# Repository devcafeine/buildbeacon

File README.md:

<!-- BuildBeacon — README (English). Version 1.12 (2026-11-12) — the Hub task builds the web interface when needed. -->
# BuildBeacon

**A wall of glowing hexagonal tiles that shows the state of your GitHub Actions — and
anything else a plugin can read.**

[Version française](README.fr.md)

Each 3D-printed tile has its own LEDs. A tile follows a project: its top and bottom strips
glow with the overall state (green, red, pulsing orange while a run is in progress), and
its five dots show the last five runs. The master tile, which holds the ESP32, shows the
state of the system.

> **Status: early development.** The Hub runs from `config.json`: GitHub plugin, LED
> rendering, output to WLED, hot reload of the configuration, REST API, web interface and
> Docker image, plus a simulator and a test pattern.

## How it works

```
GitHub API ──(polling, ETag)──┐
                              ▼
              ┌──────────── Hub (Dart) ─────────────┐
              │  source plugins → state cache       │
              │        ↓                            │
              │  LED frame (20 fps)                 │──DDP/UDP──▶ ESP32 + WLED ──▶ tiles
              │  REST API · web interface           │
              └─────────────────────────────────────┘
```

- **Hardware**: WS2812B LEDs on a single data line, driven by an ESP32-C3 running
  [WLED](https://kno.wled.ge/). No custom firmware: WLED only receives the colors.
- **Hub**: a Dart program (Docker image) that reads the sources through **plugins**,
  computes the color of every LED and streams the frames to WLED over DDP.
- **Plugins**: GitHub Actions first. Anyone can add a source (another CI, a 3D printer, a
  web service…) with the plugin SDK — see [Writing a plugin](docs/writing-a-plugin.md).

## The tiles

| Tile | LEDs | Zones |
|---|---|---|
| Master (logo, holds the ESP32) | 3 | `system` |
| Project tile | 9 | `ambient`: top and bottom strips (4 LEDs) · `dots`: 5 dots (left → right) |

Tiles are chained in wiring order: the master first (LEDs 0–2), then project tile #k uses
LEDs `3 + 9·(k−1)` to `3 + 9·k − 1`. The wiring order is independent from the place on the
wall: `config.json` stores both.

Display modes: `overall` (color of the current state), `history` (last 5 runs on the dots),
`thresholds` (a measurement compared to thresholds), `gauge` (progress bar on the dots).

The 3D models (OpenSCAD) and circuit boards (KiCad) are in [`hardware/`](hardware/README.md),
under CERN-OHL-P-2.0.

## Quick start (developers)

Requirements: [mise](https://mise.jdx.dev/), which installs the right Flutter/Dart SDK.

```sh
git clone https://github.com/devcafeine/buildbeacon.git
cd buildbeacon
mise install        # Flutter 3.47.6 (Dart 3.13.5)
mise run get        # dependencies of the whole workspace
mise run check      # format, static analysis, tests
```

### Without hardware: the simulator

The simulator is a fake WLED that shows the tiles in a web page.

```sh
mise run simulator -- --open                    # terminal 1: http://localhost:8090
mise run test-pattern -- --host 127.0.0.1       # terminal 2: sends a test pattern
```

Options: `mise run simulator -- --help`. Add `--config <config.json>` to see your real
layout, `--terminal` to draw in the terminal.

### Run the Hub

```sh
mise run hub        # then open http://localhost:8080
```

`mise run hub` first builds the web interface if its code changed (a few seconds, skipped
when up to date). On its first start, the Hub creates `data/config.json` with the master
tile only. Then open
**http://localhost:8080**: the wall drawn at its real place, with the live
colors. Select a tile to choose the source and the display mode of each zone; add a tile
with a **+**, move it by dragging it, set the chain order, WLED, the brightness and the
colors. Your changes are previewed on the wall and checked by the Hub as you type; nothing
reaches the LEDs before you **save**. Language: English or French (menu, or `?lang=fr`).

#### 3D printing

The **3D printing** tab turns your wall into the parts to print with the parametric model
of [`hardware/cad`](hardware/README.md) (OpenSCAD):

- **the parts**: a shell per tile with its name (the master tile with the logo), the back
  plate of the master tile (it holds the ESP32), one back plate for the project tiles to
  print as many times as there are tiles (they are all the same), and the "dog bones" that
  join the back plates, one per side shared by two tiles;
- **Download** gives a parameter sets file named after the model
  (`buildbeacon_tile_vX.Y.json`): put it next to the `.scad` file, open the model in OpenSCAD, pick a part in the
  Customizer list, render (**F6**) and export to STL;
- or render every part at once: the tab gives the commands to run in `hardware/cad`
  (`openscad -p … -P mise-tile -o mise-tile.stl …`), with a copy button.

Style, font and mounting stay the settings of the model; the engraved name is the name of
the tile. Before the dog bones, print `part = link_test` once to adjust their fit.

To start from an example instead: [`config.example.json`](config.example.json) follows
three public projects — BuildBeacon itself (master tile), WLED and mise — and needs no
token. Copy it before starting the Hub: `mkdir -p data && cp config.example.json
data/config.json`.

**Without tiles**, the simulator plays the part of WLED in a web page: in the interface,
**Settings** tab, set the WLED address to `127.0.0.1` and save, then in another terminal:

```sh
mise run simulator -- --open --config "$PWD/data/config.json"
```

The simulator follows `data/config.json`: tiles added, moved or renamed in the interface
show up at their place, without a reload. The Hub reloads `data/config.json` as soon as it is saved, from the
interface or by hand, and refuses an invalid version (the previous one is kept).

The Hub also serves its REST API on http://localhost:8080/api (`--port` to change it):

```sh
curl http://localhost:8080/api/state        # what the tiles show, as JSON
curl -X POST http://localhost:8080/api/tiles/wled/identify \
     -H 'Content-Type: application/json' -d '{}'   # make a tile blink
```

See [REST API](docs/api.md): routes, live events, security (`BB_API_TOKEN`).

Without a token, GitHub allows 60 requests per hour: the example polls every 180 s for
its 3 sources, and the Hub tells you if your configuration needs more. With a token
(`cp .env.example .env`, then fill `BB_GITHUB_TOKEN`), you can go down to 30 s and follow
private repositories.

### With the tiles

1. Flash [WLED](https://install.wled.me/) on the ESP32-C3, then in its web interface:
   - *LED Preferences*: data GPIO 4, type WS281x, color order GRB, length = 3 + 9 × number
     of project tiles, maximum current of your power supply;
   - *WiFi Setup*: your network, mDNS name `buildbeacon` (→ `buildbeacon.local`);
   - *Sync Interfaces*: "Receive UDP realtime" enabled (default).
2. Check the wiring and find the chain order:
   `mise run test-pattern -- --host buildbeacon.local` (or the IP of WLED).
3. Run `mise run hub` and describe your tiles in the web interface: their place on the wall
   (drag them) and the wiring order (**Chain** tab; *identify* makes a tile blink). The
   Hub checks WLED (LED count) and sets its brightness.

## Where can the Hub run?

The Hub is a small native program: very little CPU, about 50 MB of RAM. It must be on the
same network as WLED (UDP 4048, HTTP 80) and reach the Internet for the sources.

| Hardware | Supported | Notes |
|---|---|---|
| Mini PC, server or NAS, Linux x86-64 | yes | recommended: always on, [with Docker](#install-with-docker-linux) |
| Raspberry Pi 3, 4, 5, Zero 2 W with a 64-bit OS (arm64) | yes | a good choice without a server; Docker too |
| Raspberry Pi 2 or 3 with a 32-bit OS (ARMv7) | yes | published Docker image |
| macOS, Windows, Linux desktop | yes | to develop or try it out |
| Raspberry Pi 1, Zero, Zero W (ARMv6) | no | Dart does not support ARMv6 |
| ESP32 and other microcontrollers | no | the ESP32 runs WLED and only receives the colors |

Tested so far: macOS (Apple Silicon), Linux x86-64 (CI) and the Docker image (x86-64 in
the CI, arm64 with OrbStack; arm64 and ARMv7 images built and published by the CI). The other platforms
are supported by Dart but not tested yet: reports are welcome.

## Install with Docker (Linux)

The recommended setup: an always-on Linux machine on the same network as WLED — mini PC,
server, Raspberry Pi 4 or 5 with a 64-bit OS.

The image is published on GitHub for x86-64, arm64 and ARMv7
([`ghcr.io/devcafeine/buildbeacon-hub`](https://github.com/devcafeine/buildbeacon/pkgs/container/buildbeacon-hub)):
two files are enough, no need to clone the repository.

```sh
mkdir buildbeacon && cd buildbeacon
curl -fsSLO https://raw.githubusercontent.com/devcafeine/buildbeacon/main/docker-compose.yml
curl -fsSL -o .env https://raw.githubusercontent.com/devcafeine/buildbeacon/main/.env.example
# optional, in .env: BB_GITHUB_TOKEN, BB_LANG=fr, BB_PORT…
docker compose pull && docker compose up -d
```

Then open **http://<address of the machine>:8080**. On its first start, the Hub creates
its configuration with the master tile only, in the `buildbeacon-data` volume: everything
else is set up in the web interface.

- **Network**: the container uses the network of the machine (`network_mode: host`), so
  the LED frames reach WLED over UDP and `buildbeacon.local` is found by mDNS, as outside
  Docker. The interface listens on port 8080; set `BB_PORT` in `.env` to change it.
- **Update**: `docker compose pull && docker compose up -d`. **Logs**:
  `docker compose logs -f`.
- **Versions**: `latest` follows the main branch; each version also has its own tag
  (`ghcr.io/devcafeine/buildbeacon-hub:0.2.0`): put it in `docker-compose.yml` instead of
  `latest` to stay on a version, or to go back to one.
- **The image** (about 40 MB) holds the compiled Hub and its interface only, and runs as
  an unprivileged user. Secrets stay in `.env`, outside the image and the volume.
- **Build it from the sources** instead: `git clone` the repository, then
  `docker compose up -d --build` in it. It takes a few minutes the first time (it downloads
  Flutter to build the interface) and about 2 GB of RAM, on a Linux x86-64 or arm64
  machine.
- **On macOS or Windows**, Docker runs in a virtual machine: set the IP address of WLED, as
  mDNS does not reach the local network from there. To try BuildBeacon on these systems,
  `mise run hub` is simpler.

## Configuration

`config.json` (edited from the web interface, by hand or through the
[REST API](docs/api.md)):

```json
{
  "version": 1,
  "wled": { "host": "buildbeacon.local", "brightness": 128 },
  "poll_seconds": 30,
  "tiles": [
    { "id": "master", "label": "BuildBeacon", "kind": "master", "chain_index": 0,
      "pos": { "q": 0, "r": 1 }, "zones": { "system": null } },
    { "id": "app", "label": "App", "kind": "project", "chain_index": 1,
      "pos": { "q": 0, "r": 0 },
      "zones": {
        "ambient": { "source": { "type": "github", "repo": "owner/app", "workflow": "ci.yml" },
                     "mode": "overall" },
        "dots":    { "source": { "type": "github", "repo": "owner/app", "workflow": "ci.yml" },
                     "mode": "history" } } }
  ]
}
```

Secrets never go into `config.json`: the GitHub token (fine-grained, read-only, *Actions:
read* and *Metadata: read*) is given through the `BB_GITHUB_TOKEN` environment variable —
see [`.env.example`](.env.example). The REST API never returns a secret.

## Languages

The interfaces are available in English and French (`BB_LANG=en` or `BB_LANG=fr` for the
command-line tools; for the web pages, the browser language or the language menu). Plugins
bring their own translations.

## Repository

```
hub/                 Dart workspace
  sdk/               plugin SDK (the only dependency of a plugin)
  core/              model, LED rendering, plugin registry
  plugins/github/    GitHub Actions plugin
  server/            the Hub (bin/hub.dart), REST API, DDP output, simulator, test pattern
  ui/                web interface (Flutter Web), served by the Hub
  Dockerfile         Docker image of the Hub and its interface
  tool/              new_plugin.dart (mise run new-plugin <name>)
docs/                guides, REST API
hardware/            3D models (cad/), circuit boards (pcb/), build guide
config.example.json example configuration (public repositories)
docker-compose.yml  the Hub in Docker (docker compose up -d --build)
```

## Contributing

Bug reports, ideas, plugins and translations are welcome: see
[CONTRIBUTING.md](CONTRIBUTING.md) and [Writing a plugin](docs/writing-a-plugin.md).

## License

Software: [MIT](LICENSE). Hardware (3D models, boards, in `hardware/`):
[CERN-OHL-P-2.0](hardware/LICENSE). The web interface embeds the Roboto font
([Apache License 2.0](hub/ui/assets/fonts/Roboto_LICENSE.txt)).

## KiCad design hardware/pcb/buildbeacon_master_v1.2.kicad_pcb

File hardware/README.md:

<!-- BuildBeacon — hardware (English). Version 1.9 (2026-11-13) — model v1.7 -->
# BuildBeacon — hardware

[Version française](README.fr.md)

Everything you need to build the tiles: parametric 3D models (OpenSCAD) and circuit boards
(KiCad), licensed under [CERN-OHL-P-2.0](LICENSE).

> **Status:** the 3D models are printed and tested. The **v1.2** boards are ordered and
> **not yet validated** on a real tile: wait for feedback from the first build before ordering
> many, or build without boards (see [Building without boards](#building-without-boards)).

## Contents

```
hardware/
  cad/buildbeacon_tile_v1.7.scad      tiles, back plates, stand, Skådis clips… (OpenSCAD)
  pcb/buildbeacon_tuile_v1.2.kicad_pcb    project tile board (9 LEDs)
  pcb/buildbeacon_master_v1.2.kicad_pcb   master tile board (ESP32-C3 + 3 LEDs)
  pcb/gen_buildbeacon_pcb_v1.2.py     Python script that generates both boards
  images/                             KiCad 3D renders of the boards
  LICENSE                             CERN-OHL-P-2.0
```

File names and on-board labels are in French: *tuile* = tile, *ALIM* = power input,
*cavaliers* = solder jumpers, *1 goutte d'étain par bloc* = one solder blob per block.

## Overview

- Each hexagonal tile (80 mm across flats) holds a round board carrying short pieces of
  **WS2812B LED strip** (5 V, 100 LEDs/m, 10 mm wide).
- All LEDs form **a single data chain**, driven by an **ESP32-C3 SuperMini** running
  [WLED](https://kno.wled.ge/), housed in the **master** tile.
- Each board has **6 JST PH 3-pin connectors**, one per side of the hexagon (5 on the
  master: the 6th side is taken by USB). Neighbouring tiles are linked with short JST cables.
  The input and output sides are **selected with solder jumpers**, so tiles can be arranged
  in any shape.
- Same pinout on every connector: **1 = +5 V, 2 = data, 3 = GND**. Cables are "same
  direction" (pin 1 to pin 1).

| Tile | LEDs | Position in the chain |
|---|---|---|
| Master | 3 | LEDs 0 to 2 |
| Project tile no. k | 9: 2 at the top, 5 dots in the middle, 2 at the bottom | LEDs `3 + 9·(k−1)` to `3 + 9·k − 1` |

Inside a project tile, data enters the top strip (left → right), goes through the 5 dots
(right → left), then the bottom strip (left → right). The Hub knows this order.

## Circuit boards

| | Front | Back |
|---|---|---|
| **Project tile** |  |  |
| **Master** |  |  |

2-layer, 1.6 mm boards. Front: LED strips, resistors, capacitor, ESP32 (master). Back: JST
connectors and solder jumpers. Copper pours: +5 V on the front, GND on the back.

### Ordering the boards

1. Open the `.kicad_pcb` file in **KiCad 8 or 9** and save it once (KiCad reports an old
   file format: this is expected, the file is generated by a script).
2. **Press B** to fill the copper zones. *Skip this and the +5 V and GND pours will not be
   manufactured.*
3. Run the **DRC**: 0 errors expected.
4. Export Gerbers and drill files, then order: 2 layers, 1.6 mm, HASL, any colour. The
   boards are designed for hand soldering; no factory assembly is needed.

### Bill of materials

**Project tile** (per tile)

| Ref | Part | Notes |
|---|---|---|
| — | Board `buildbeacon_tuile_v1.2` | |
| RB1, RB2, RB3 | WS2812B strip, 5 V, 100 LEDs/m, 10 mm: pieces of 2, 5 and 2 LEDs | follow the "DIN >>>" arrows |
| R1 | 330 Ω resistor, ¼ W, through-hole | 220 to 470 Ω is fine |
| R2 | 10 kΩ resistor, ¼ W, through-hole | 10 to 100 kΩ is fine; prevents flicker when the input floats |
| C1 | 10 µF 16 V electrolytic capacitor, 5 mm pitch | laid flat, **+ on the square pad** |
| J1 to J6 | JST PH S3B-PH-SM4-TB (SMD, horizontal, 2 mm pitch) | only on the sides you use (at least 1 in, 1 out) |
| — | 2 solder blobs | 1 in the IN block, 1 in the OUT block |

**Master tile**

| Ref | Part | Notes |
|---|---|---|
| — | Board `buildbeacon_master_v1.2` | |
| U1 | ESP32-C3 SuperMini + pin headers | USB towards the edge marked "USB" |
| RB1 | WS2812B strip: piece of 3 LEDs | |
| D1 | 1N4148 (or 1N4001 to 1N4007) | **band towards the square pad**, see below |
| R1 | 330 Ω resistor | between GPIO 4 and the strip |
| C1 | 10 µF 16 V electrolytic | **+ on the square pad** |
| J1 to J4, J6 | JST PH S3B-PH-SM4-TB | used sides only |
| J7 | 5 V input "ALIM" (2 wires or a 5.08 mm terminal block) | optional, see [Power](#power) |
| — | 1 solder blob | OUT block |

**Common**: JST PH 3-pin double-ended "same direction" cables, M2.5 × 4 × 3.5 brass inserts
+ M2.5 × 6 screws to hold the board, M3 × 5 × 4 inserts + M3 screws (or 6 × 3 mm magnets) to
close the tile.

### Shopping list

For a setup of **1 master + N project tiles** (example: N = 4).

| Item | Quantity | Example N = 4 |
|---|---|---|
| Board `buildbeacon_master_v1.2` | 1 | 1 |
| Board `buildbeacon_tuile_v1.2` | N | 4 |
| ESP32-C3 SuperMini (with pin headers) | 1 | 1 |
| WS2812B strip, 5 V, 100 LEDs/m, 10 mm | 3 + 9 × N LEDs (1 m = 100 LEDs, up to 10 tiles) | 39 LEDs → 1 m |
| 330 Ω ¼ W resistor | N + 1 | 5 |
| 10 kΩ ¼ W resistor | N | 4 |
| 10 µF 16 V electrolytic capacitor, 5 mm pitch | N + 1 | 5 |
| 1N4148 diode (or 1N4001 to 1N4007) | 1 | 1 |
| JST PH S3B-PH-SM4-TB connector | at least 2 × N (2 per project tile, 1 on the master and on the last tile); up to 6 × N + 5 to allow any layout | 8 to 29 |
| JST PH 3-pin double-ended "same direction" cable | N (one per link between two tiles) | 4 |
| M2.5 × 4 × 3.5 brass insert + M2.5 × 6 screw (board mounting) | 4 × (N + 1) | 20 + 20 |
| Tile closing: 6 × 3 mm magnets **or** M3 × 5 × 4 inserts + M3 screws | 6 × (N + 1) magnets **or** 3 × (N + 1) inserts and screws | 30 magnets or 15 + 15 |
| USB-C cable | 1 | 1 |
| 5 V power supply (optional, on J7 "ALIM") | at least 0.6 A × N (see [Power](#power)) | 5 V 3 A |
| 2-pin 5.08 mm terminal block (optional, J7) | 1 | 1 |
| White or "natural" PLA or PETG filament | shells, back plates, links, stand or clips | |

Board makers often ship a minimum of 5 boards per design.
For [building without boards](#building-without-boards), you only need the ESP32, the
strip, one 330 Ω resistor, the tile closing parts and the power supply, plus 22 to 28 AWG
silicone wire (3 wires per link).

### Tools

- 3D printer.
- Fine-tip soldering iron (the JST connectors are SMD), solder, flux.
- Desoldering braid (to move a jumper blob).
- Scissors or a cutter to cut the LED strip on its cut marks.
- Side cutters, tweezers; a multimeter is recommended (check there is no short between +5 V
  and GND before powering up for the first time).
- A computer to install WLED on the ESP32 (see [Configuring WLED](#configuring-wled)).

### Why D1 on the master?

The ESP32 sends 3.3 V data, while LEDs powered at 5 V expect at least about 3.5 V: at high
brightness the first LED misreads the signal and the chain flickers. D1 drops the supply of
the 3 master LEDs by about 0.7 V (≈ 4.4 V): they then read the 3.3 V signal reliably and pass
it on at 5 V to the following tiles.

### Solder jumpers: choosing input and output

On the back, the jumpers are grouped in blocks of 6 rows numbered **1 to 6**, like the sides
(each side's number is printed next to its connector).

- **Project tile**: **IN** block = side where data comes in; **OUT** block = side towards the
  next tile. **One solder blob per block**, bridging the two pads of the chosen row.
  Example: data arrives on side 4 and leaves on side 1 → blob on row 4 of IN and row 1 of OUT.
- **Master**: a single **OUT** block (sides 1, 2, 3, 4 and 6).
- The last tile of the chain needs no blob in its OUT block.
- To change it: remove the blob with desoldering braid.

### Power

- **Small setup** (master + 2 or 3 tiles, limited brightness): the ESP32's USB-C is enough.
- **More tiles**: external 5 V supply on the master's **J7 "ALIM"** (square = +5 V,
  round = GND). +5 V and GND run through every JST connector.
- **Never connect USB and the external supply at the same time.** Unplug the external supply
  before flashing the ESP32.
- Budget up to 60 mA per LED at full white (≈ 0.55 A per project tile). Set WLED's current
  limiter to your supply's rating (850 to 1,500 mA on USB).
- Recommended brightness: start at 128 (50 %).

### Regenerating the boards

The boards are produced by `gen_buildbeacon_pcb_v1.2.py` (Python 3, no dependencies):

```sh
cd hardware/pcb
python3 gen_buildbeacon_pcb_v1.2.py          # project tile
python3 gen_buildbeacon_pcb_v1.2.py --logo   # master
```

Any board change bumps the script's `VERSION` variable (and so the file names and the text
printed on the back of the board).

## 3D models

A single parametric file: [`cad/buildbeacon_tile_v1.7.scad`](cad/buildbeacon_tile_v1.7.scad),
to open in [OpenSCAD](https://openscad.org/) (2021 or later). Set the parameters in the
**Customizer**, pick the part with `part`, render (**F6**) and export to STL.

**From the web interface of the Hub**: the **3D printing** tab lists the parts of your wall
(a shell per tile with its name, the back plates, the dog bones) and downloads
`buildbeacon_tile_v1.7.json`, one parameter set per part. Put it next to the `.scad` file:
the Customizer offers the sets in its list, ready to render; the tab also gives the
commands that render every part at once (`openscad -p … -P <set> -o <set>.stl`).

### Parts (`part`)

| `part` | Part |
|---|---|
| `tile` | tile shell (face with the text) |
| `back` | back plate (holds the LEDs or the board) |
| `both` | both, for preview |
| `links` / `link_test` | "dog bones" joining the back plates / 4 test bones for fit |
| `magnet_test` | pieces of two neighbouring tiles to try the tile-to-tile magnets |
| `stand` | desk stand (tiles in a row) |
| `skadis_clips` | clips for an IKEA Skådis pegboard |
| `cable_clips`, `plugs` | cable clips, notch plugs |
| `letters`, `base`, `led_bridge`, `knockout_test` | options (see the comments in the file) |

### Main settings

- **Text**: `label` (project name), `label2`, `font`, `text_size`. Master tile:
  `master = true` and `master_logo = true` (logo instead of a name).
- **Style**: `glow` (one colour, thinned text shines brighter), `swap` (filament change:
  black face, white letters), `dark_face`, `stencil`.
- **With the boards**: `led_mount = "pcb"`, `pcb_fix = "insert"` (M2.5 × 4 × 3.5 inserts,
  hole `pcb_insert_d = 3.2`).
- **Closing the tile**: `screw_type = "magnet"` (6 × 3 mm magnets) or `"insert"` (M3 × 5 × 4
  inserts, hole `insert_d = 3.6`).
- **Joining the plates**: `link_fit` sets how tight the dog bones are; print
  `part = "link_test"` first to find the right value.
- **Tile-to-tile magnets** (being tested, off by default): `link_magnets = true` puts one
  6 × 3 mm magnet per side in a boss of the back plate, behind a 0.6 mm skin of the shell
  (`link_mag_skin`): tiles snap together and come off one by one, nothing shows outside.
  Print `part = "magnet_test"` first: it checks the fit and the hold (instructions in the
  comments of the file).

### Printing

- White or "natural" PLA or PETG for the shell (light shines through the face).
- Shell: **face down on the bed**, no supports. Back plate: ribs up. Stand and clips: flat.
- Brass inserts go in with a soldering iron (≈ 220 °C for PLA).

## Building without boards

With `led_mount = "strip"`, the strip pieces are glued straight onto the back plate between
rails and wired together (3 silicone wires, 22 to 28 AWG). Same chain order, same LEDs, no
boards to order. Add a 330 Ω resistor between the ESP32's GPIO 4 and the first LED.

## Configuring WLED

See the [main README](../README.md#with-the-tiles): GPIO 4, WS281x, GRB order,
length = 3 + 9 × number of project tiles, current limiter set.

## License

Hardware (this folder): [CERN-OHL-P-2.0](LICENSE). Software: [MIT](../LICENSE).

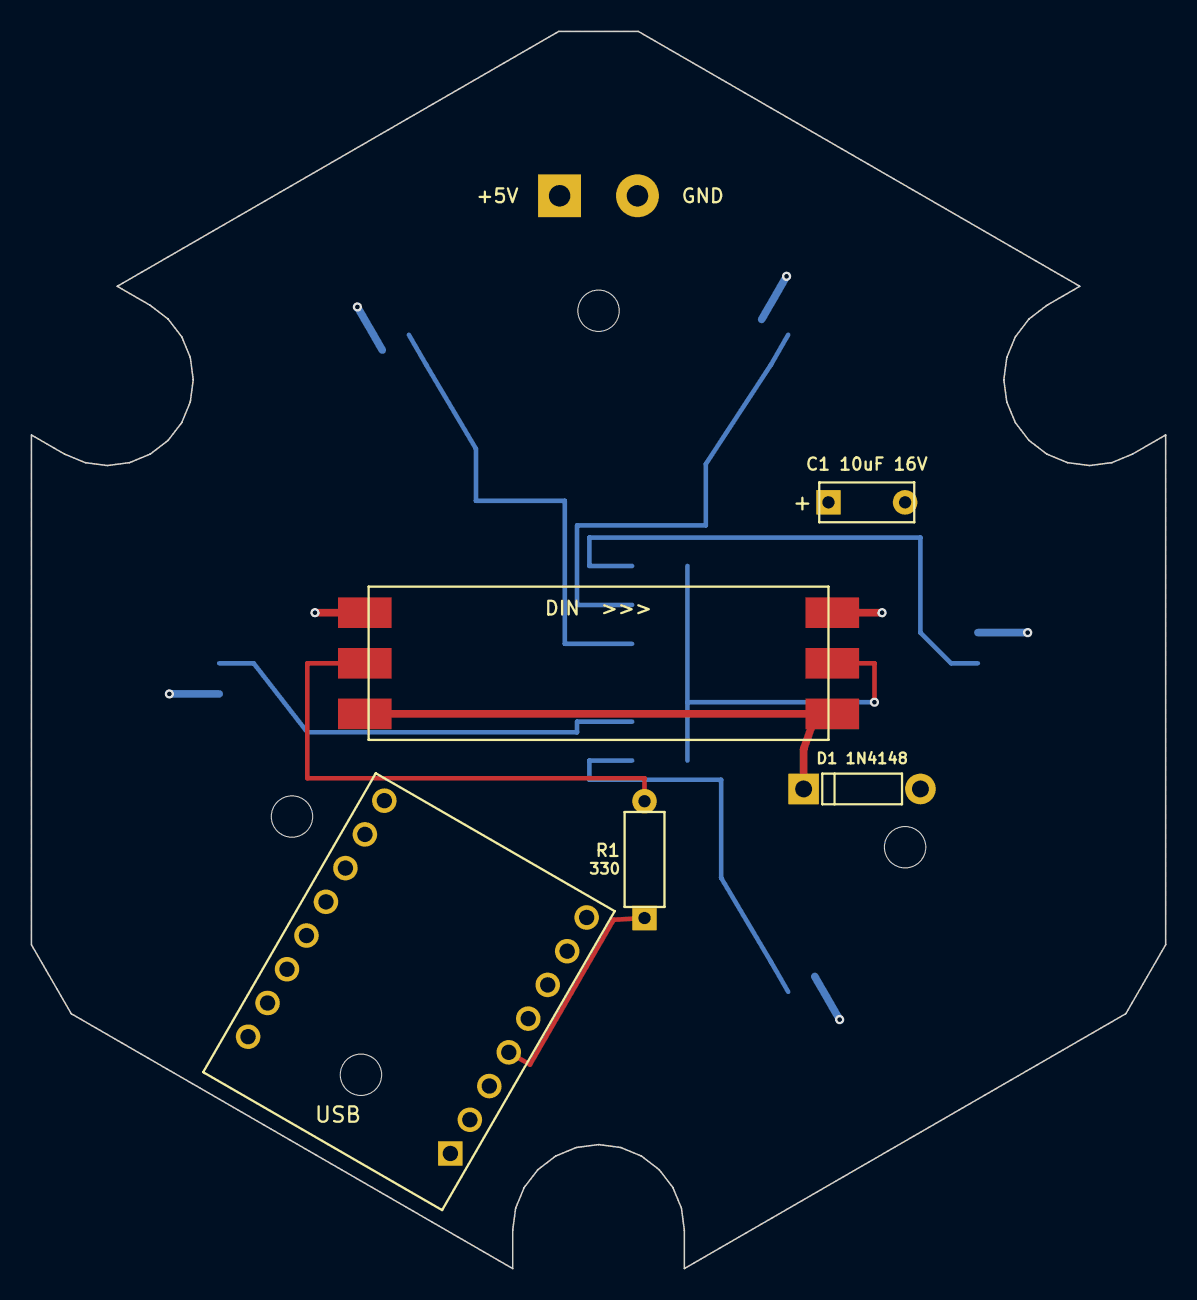
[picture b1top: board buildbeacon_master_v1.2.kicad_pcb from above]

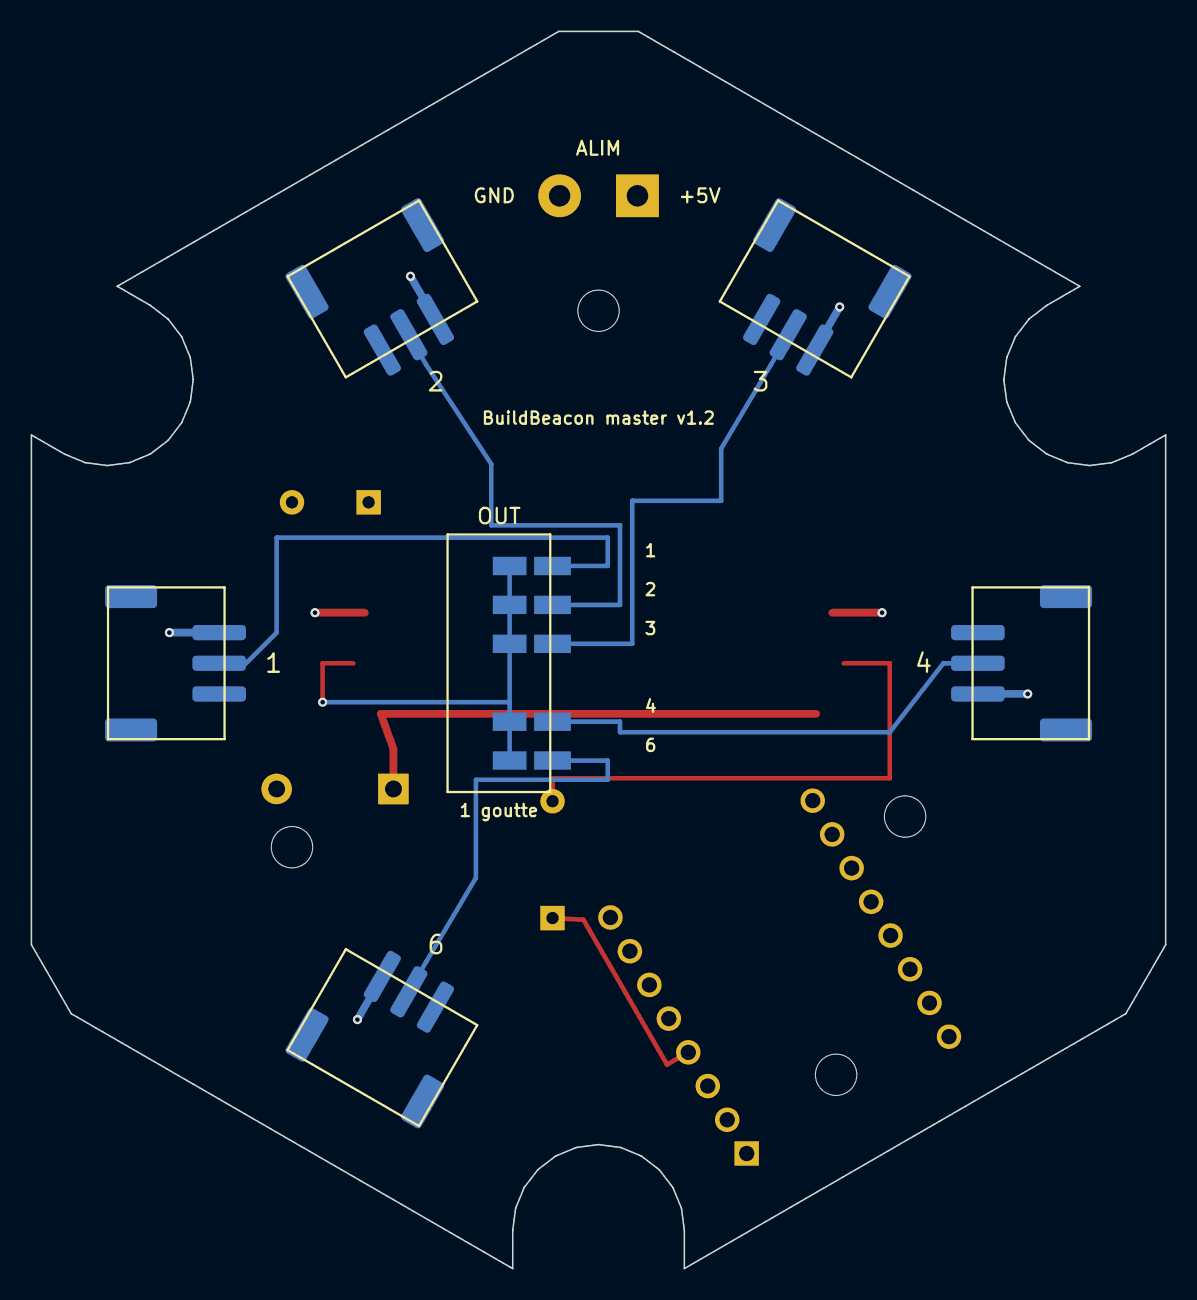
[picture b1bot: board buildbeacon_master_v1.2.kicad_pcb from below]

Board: 2 copper layers, 74.0 x 80.7 mm, 16 parts (6 on the bottom side), 11 nets.

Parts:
C1: 10uF; C_P5.00
D1: 1N4148/1N4007; D_DO-41_P7.62
H1, H2, H3, H4: M2.5; MountingHole_M2.5
J1, J2, J3, J4, J6: JST_PH_S3B-PH-SM4-TB_1x03-1MP_P2.00mm_Horizontal
J7: ALIM 5V; Alim_5V_P5.08
R1: 330; R_Axial_P7.62
RB1: Ruban_WS2812B_10mm
SW_OUT: SolderJumper_x5_P2.54
U1: ESP32-C3 SuperMini; ESP32-C3_SuperMini

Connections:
+5V: C1.1, D1.2, J1.1, J2.1, J3.1, J4.1, J6.1, J7.1, U1.L1
DO: RB1.OUT_D, SW_OUT.1B, SW_OUT.2B, SW_OUT.3B, SW_OUT.4B, SW_OUT.6B
GND: C1.2, J1.3, J1.MP, J2.3, J2.MP, J3.3, J3.MP, J4.3, J4.MP, J6.3, J6.MP, J7.2, RB1.IN_GND, RB1.OUT_GND, U1.L2
GPIO4: R1.1, U1.L4
S1_DIN: R1.2, RB1.IN_D
SIDE1: J1.2, SW_OUT.1S
SIDE2: J2.2, SW_OUT.2S
SIDE3: J3.2, SW_OUT.3S
SIDE4: J4.2, SW_OUT.4S
SIDE6: J6.2, SW_OUT.6S
VLED: D1.1, RB1.IN_5V, RB1.OUT_5V

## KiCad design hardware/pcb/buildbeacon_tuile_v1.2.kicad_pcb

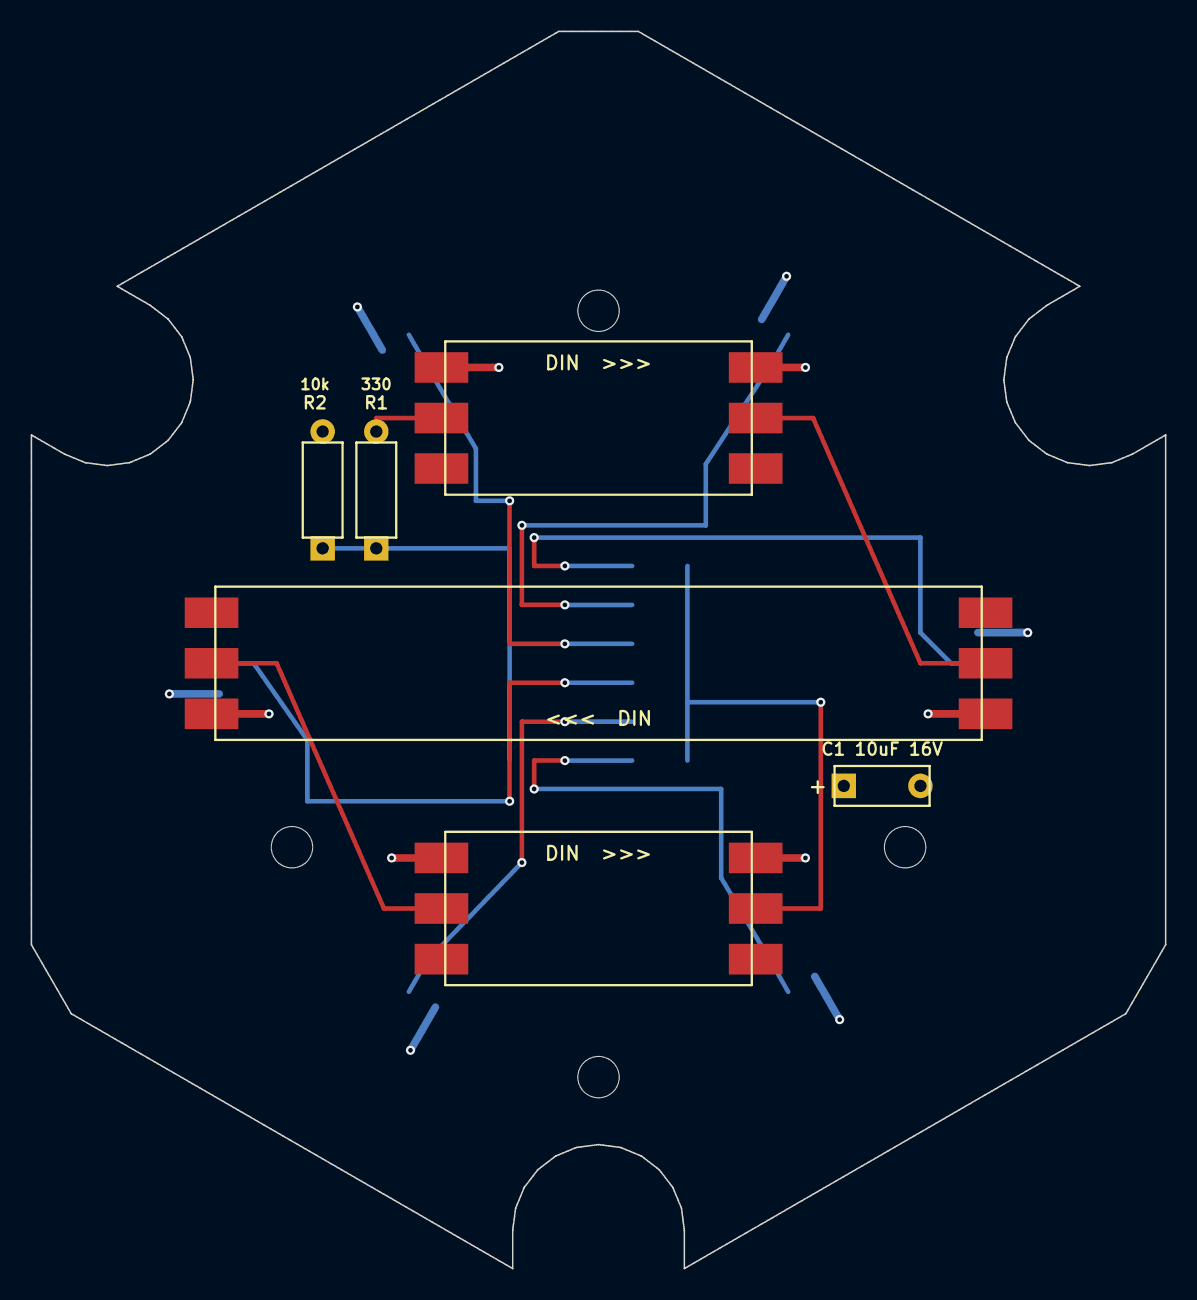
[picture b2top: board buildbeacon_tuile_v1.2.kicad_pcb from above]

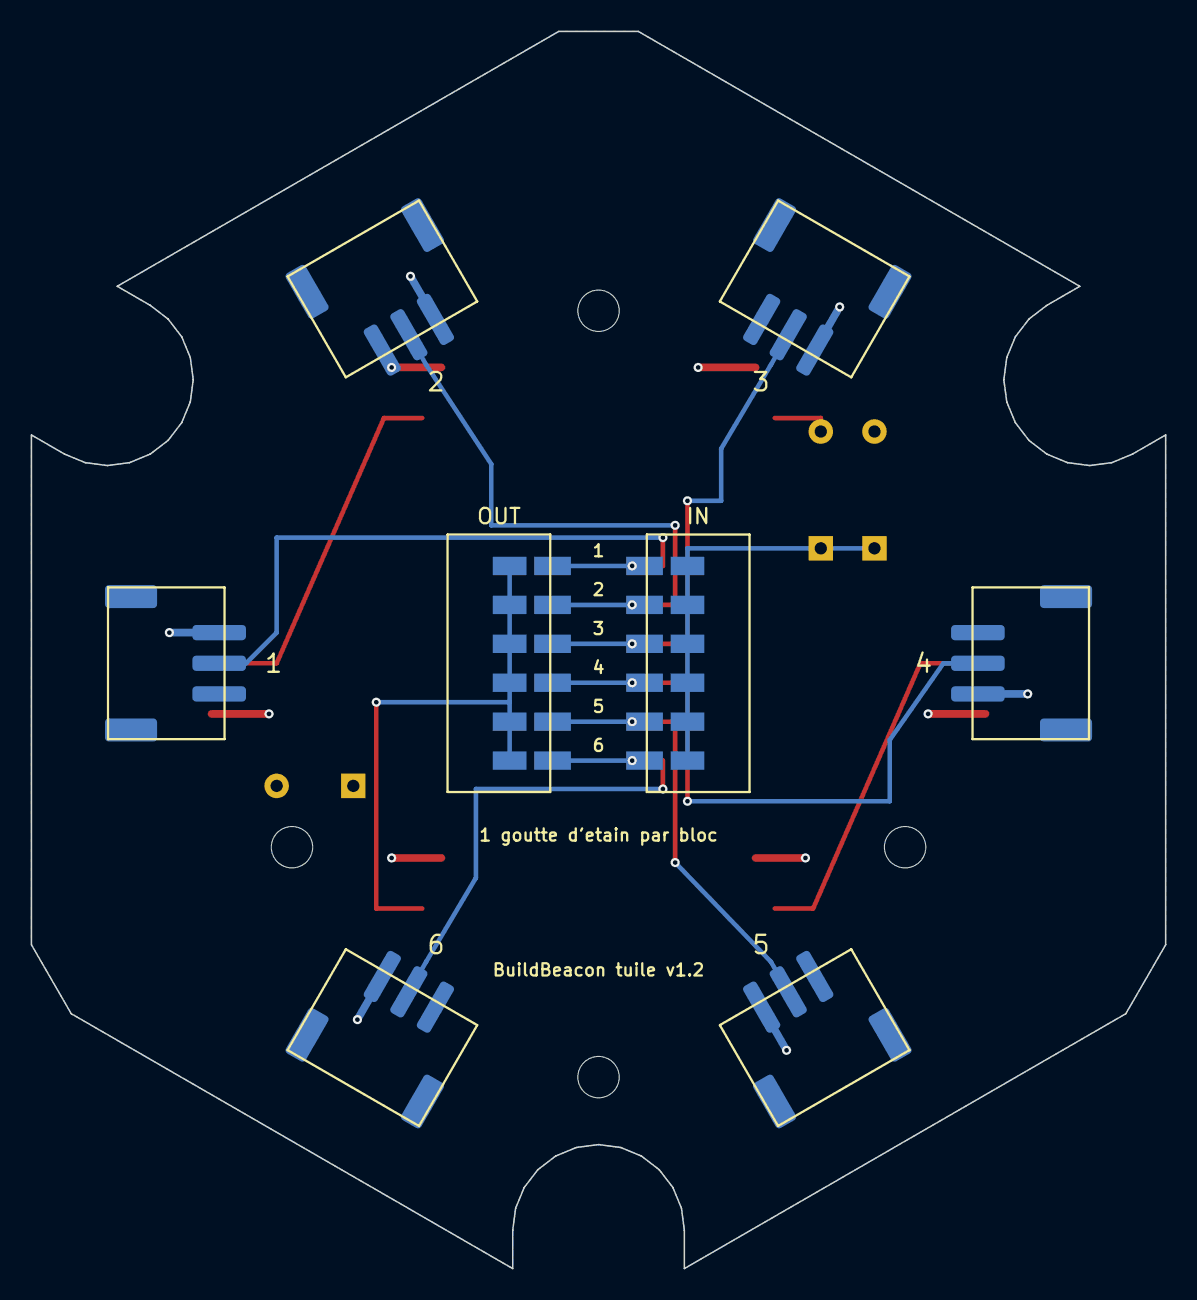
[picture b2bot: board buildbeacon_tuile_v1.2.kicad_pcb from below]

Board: 2 copper layers, 74.0 x 80.7 mm, 18 parts (8 on the bottom side), 13 nets.

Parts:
C1: 10uF; C_P5.00
H1, H2, H3, H4: M2.5; MountingHole_M2.5
J1, J2, J3, J4, J5, J6: JST_PH_S3B-PH-SM4-TB_1x03-1MP_P2.00mm_Horizontal
R1: 330; R_Axial_P7.62
R2: 10k; R_Axial_P7.62
RB1, RB2, RB3: Ruban_WS2812B_10mm
SW_IN: SolderJumper_x6_P2.54
SW_OUT: SolderJumper_x6_P2.54

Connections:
+5V: C1.1, J1.1, J2.1, J3.1, J4.1, J5.1, J6.1, RB1.IN_5V, RB1.OUT_5V, RB2.IN_5V, RB2.OUT_5V, RB3.IN_5V, RB3.OUT_5V
DI: R1.1, R2.1, SW_IN.1B, SW_IN.2B, SW_IN.3B, SW_IN.4B, SW_IN.5B, SW_IN.6B
DO: RB3.OUT_D, SW_OUT.1B, SW_OUT.2B, SW_OUT.3B, SW_OUT.4B, SW_OUT.5B, SW_OUT.6B
GND: C1.2, J1.3, J1.MP, J2.3, J2.MP, J3.3, J3.MP, J4.3, J4.MP, J5.3, J5.MP, J6.3, J6.MP, R2.2, RB1.IN_GND, RB1.OUT_GND, RB2.IN_GND, RB2.OUT_GND, RB3.IN_GND, RB3.OUT_GND
S1_DIN: R1.2, RB1.IN_D
S2_DIN: RB1.OUT_D, RB2.IN_D
S3_DIN: RB2.OUT_D, RB3.IN_D
SIDE1: J1.2, SW_IN.1S, SW_OUT.1S
SIDE2: J2.2, SW_IN.2S, SW_OUT.2S
SIDE3: J3.2, SW_IN.3S, SW_OUT.3S
SIDE4: J4.2, SW_IN.4S, SW_OUT.4S
SIDE5: J5.2, SW_IN.5S, SW_OUT.5S
SIDE6: J6.2, SW_IN.6S, SW_OUT.6S

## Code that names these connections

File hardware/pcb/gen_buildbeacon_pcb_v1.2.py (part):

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MASTER = "--logo" in sys.argv
VERSION = "1.2"          # a incrementer a chaque modification de carte
OUTFILE = ("buildbeacon_master_v%s.kicad_pcb" if MASTER else "buildbeacon_tuile_v%s.kicad_pcb") % VERSION
NETS[:] = ["", "+5V", "GND", "DI", "DO", "S1_DIN", "S2_DIN", "S3_DIN"] + ["SIDE%d" % i for i in range(1, 7)] + ["GPIO4", "VLED"]
NID.clear(); NID.update({n: i for i, n in enumerate(NETS)})

RP = 34.0                                   # hexagone : sommets vers le milieu des cotes de la tuile
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else:
    ROW, FIRST, R_PORT = 15.24, 3.47, 36.0
    LEFT = ["5V", "GND", "3V3", "4", "3", "2", "1", "0"]; RIGHT = ["5", "6", "7", "8", "9", "10", "20", "21"]
    NETMAP = {"5V": "+5V", "GND": "GND", "4": "GPIO4"}
    pads = []
    for i in range(8):
        r = R_PORT - FIRST - i * 2.54
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    gr_text("D1 1N4148", 17.2, -6.2, 0.7)
    track([(13.38, -8.2), (13.38, -5.6), (14.2, st["5V"])], "VLED", 0.5)
    track([(-14.2, st["5V"]), (14.2, st["5V"])], "VLED", 0.5)   # double le 5V interne du ruban
    two("R_Axial_P7.62", "R1", "330", 3, -16.62, 3, -9.0, "GPIO4", "S1_DIN")
    gr_rect(1.7, -15.9, 4.3, -9.7); gr_text("R1", 0.6, -12.2, 0.8); gr_text("330", 0.4, -13.4, 0.7)
    g4 = mp(R_PORT - FIRST - 3 * 2.54, ROW / 2)
    track([g4, mp(R_PORT - FIRST - 3 * 2.54, ROW / 2 + 1.6), mp(14, ROW / 2 + 1.6), (3, -16.62)], "GPIO4")
    track([(3, -9.0), (3, -7.5), (-19, -7.5), (-19, 0), (-16, 0)], "S1_DIN")
    dip("SW_OUT", CX, side_net, lambda y: "DO")
    track([(BX, -6.35), (BX, 6.35)], "DO", 0.3, B)
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

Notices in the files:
hardware/pcb/gen_buildbeacon_pcb_v1.2.py:
Source : https://github.com/devcafeine/buildbeacon (hardware/pcb) - Licence : CERN-OHL-P-2.0
s") (date "%s") (rev "v%s") (comment 1 "CERN-OHL-P-2.0"))' % ("master" if MASTER else "tuile", __import__("datetime").date.today().isoformat(), VERSION),
README.md:
License: MIT
